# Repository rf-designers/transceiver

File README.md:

# YO6SSW SDR transceiver

Tayloe enabled SDR frontend.

## Designers

- Frédéric Boes
- Adrian Scripcă

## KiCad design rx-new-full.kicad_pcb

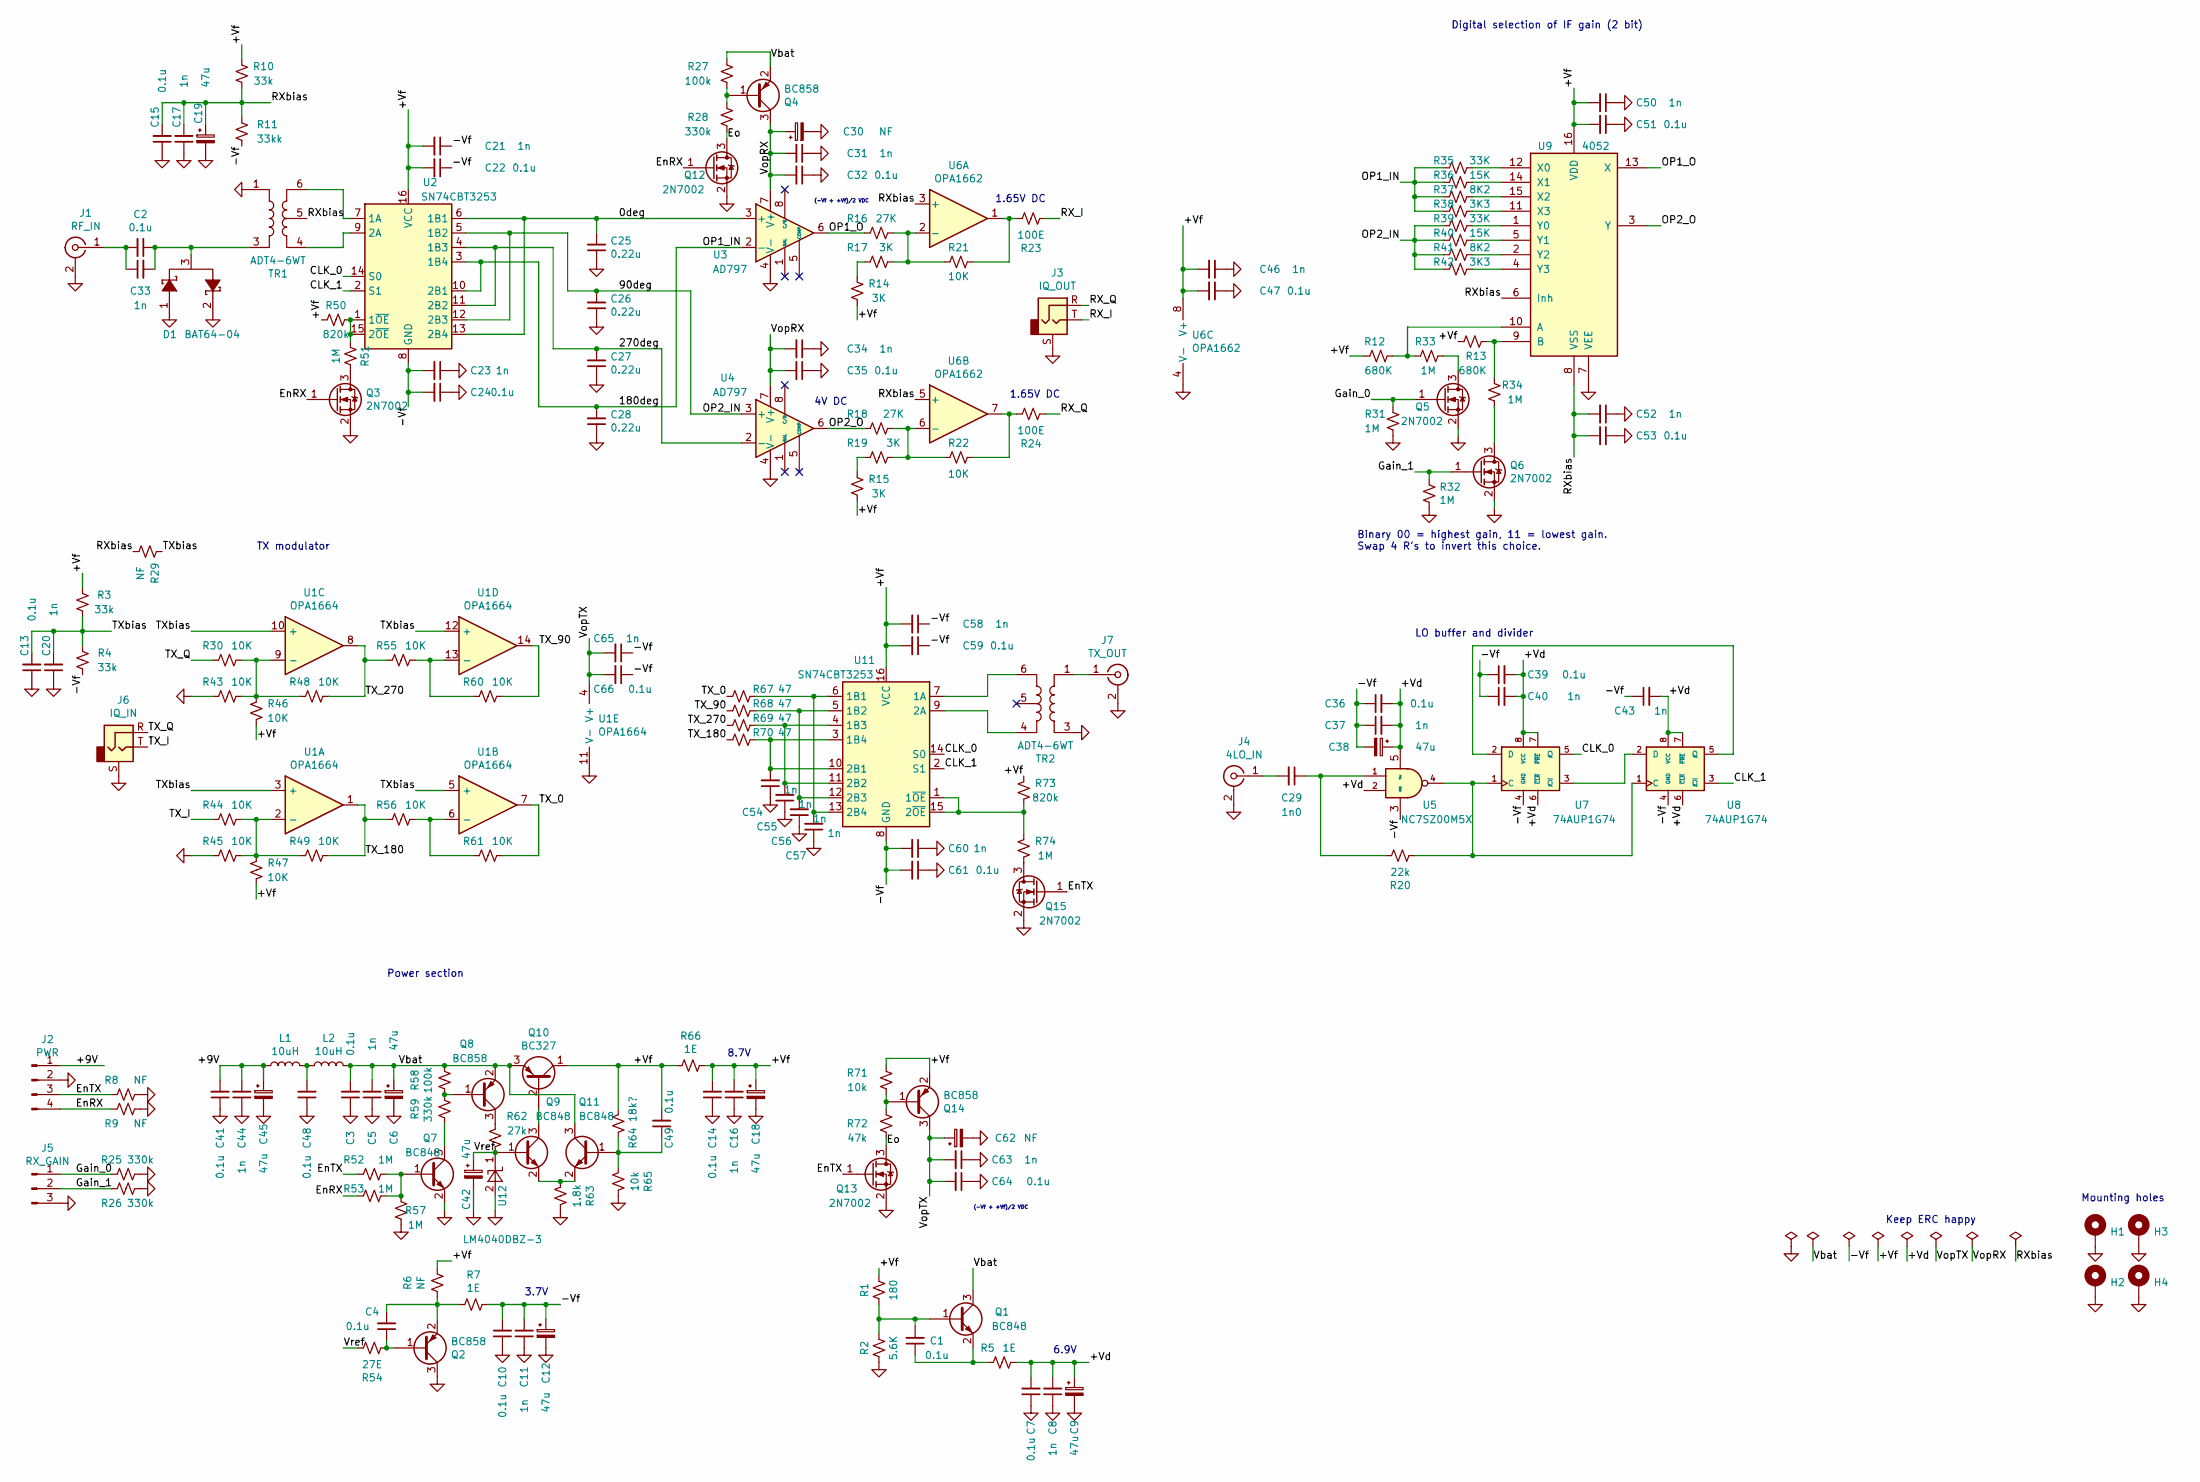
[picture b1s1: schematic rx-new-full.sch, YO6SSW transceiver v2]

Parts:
C1, C2, C3, C4, C7, C10, C13, C14, C15, C22, C24, C32, C35, C36, C39, C41, C47, C48, C49, C51, C53, C59, C61, C64, C66: 0.1u; C_0805_2012Metric_Pad1.15x1.40mm_HandSolder
C5, C8, C11, C16, C17, C20, C21, C23, C31, C33, C34, C37, C40, C43, C44, C46, C50, C52, C54, C55, C56, C57, C58, C60, C63, C65: 1n; C_0805_2012Metric_Pad1.15x1.40mm_HandSolder
C6, C9, C12, C18, C19, C38, C42, C45: 47u; CP_1210_3225Metric_Pad1.42x2.65mm_HandSolder
C25, C26, C27, C28: 0.22u; C_0805_2012Metric_Pad1.15x1.40mm_HandSolder
C29: 1n0; C_0805_2012Metric_Pad1.15x1.40mm_HandSolder
C30, C62: NF; CP_1210_3225Metric_Pad1.42x2.65mm_HandSolder
D1: BAT64-04; SOT-23
H1, H2, H3, H4: MountingHole_Pad; MountingHole_3.2mm_M3_DIN965_Pad
J1: RF_IN; SMA_Amphenol_901-144_Vertical
J2: PWR; PinHeader_1x04_P2.54mm_Vertical
J3: IQ_OUT; Jack_3.5mm_CUI_SJ1-3533NG_Horizontal; MPN SJ1-3533NG
J4: 4LO_IN; SMA_Amphenol_901-144_Vertical
J5: RX_GAIN; PinHeader_1x03_P2.54mm_Vertical
J6: IQ_IN; Jack_3.5mm_CUI_SJ1-3533NG_Horizontal; MPN SJ1-3533NG
J7: TX_OUT; SMA_Amphenol_901-144_Vertical
L1, L2: 10uH; L_0805_2012Metric_Pad1.15x1.40mm_HandSolder
Q1, Q7, Q9, Q11: BC848; SOT-23
Q2, Q4, Q8, Q14: BC858; SOT-23
Q3, Q5, Q6, Q12, Q13, Q15: 2N7002; SOT-23
Q10: BC327; TO-92_Inline
R1: 180; R_0805_2012Metric_Pad1.15x1.40mm_HandSolder
R2: 5.6K; R_0805_2012Metric_Pad1.15x1.40mm_HandSolder
R3, R4, R10: 33k; R_0805_2012Metric_Pad1.15x1.40mm_HandSolder
R5, R7, R66: 1E; R_0805_2012Metric_Pad1.15x1.40mm_HandSolder
R6, R8, R9, R29: NF; R_0805_2012Metric_Pad1.15x1.40mm_HandSolder
R11: 33kk; R_0805_2012Metric_Pad1.15x1.40mm_HandSolder
R12, R13: 680K; R_0805_2012Metric_Pad1.15x1.40mm_HandSolder
R14, R15, R17, R19: 3K; R_0805_2012Metric_Pad1.15x1.40mm_HandSolder
R16, R18: 27K; R_0805_2012Metric_Pad1.15x1.40mm_HandSolder
R20: 22k; R_0805_2012Metric_Pad1.15x1.40mm_HandSolder
R21, R22, R30, R43, R44, R45, R46, R47, R48, R49, R55, R56, R60, R61: 10K; R_0805_2012Metric_Pad1.15x1.40mm_HandSolder
R23, R24: 100E; R_0805_2012Metric_Pad1.15x1.40mm_HandSolder
R25, R26, R28, R59: 330k; R_0805_2012Metric_Pad1.15x1.40mm_HandSolder
R27, R58: 100k; R_0805_2012Metric_Pad1.15x1.40mm_HandSolder
R31, R32, R33, R34, R51, R52, R53, R57, R74: 1M; R_0805_2012Metric_Pad1.15x1.40mm_HandSolder
R35, R39: 33K; R_0805_2012Metric_Pad1.15x1.40mm_HandSolder
R36, R40: 15K; R_0805_2012Metric_Pad1.15x1.40mm_HandSolder
R37, R41: 8K2; R_0805_2012Metric_Pad1.15x1.40mm_HandSolder
R38, R42: 3K3; R_0805_2012Metric_Pad1.15x1.40mm_HandSolder
R50, R73: 820k; R_0805_2012Metric_Pad1.15x1.40mm_HandSolder
R54: 27E; R_0805_2012Metric_Pad1.15x1.40mm_HandSolder
R62: 27k; R_0805_2012Metric_Pad1.15x1.40mm_HandSolder
R63: 1.8k; R_0805_2012Metric_Pad1.15x1.40mm_HandSolder
R64: 18k?; R_0805_2012Metric_Pad1.15x1.40mm_HandSolder
R65, R71: 10k; R_0805_2012Metric_Pad1.15x1.40mm_HandSolder
R67, R68, R69, R70: 47; R_0805_2012Metric_Pad1.15x1.40mm_HandSolder
R72: 47k; R_0805_2012Metric_Pad1.15x1.40mm_HandSolder
TR1, TR2: ADT4-6WT; Mini-Circuits_CD636_H4.11mm
U1: OPA1664; SO-14_3.9x8.65mm_P1.27mm
U2, U11: SN74CBT3253; SOP-16_4.4x10.4mm_P1.27mm
U3, U4: AD797; SOIC-8_3.9x4.9mm_P1.27mm
U5: NC7SZ00M5X; SOT-23-5_HandSoldering
U6: OPA1662; SOIC-8_3.9x4.9mm_P1.27mm
U7, U8: 74AUP1G74; VSSOP-8_2.4x2.1mm_P0.5mm
U9: 4052; SOP-16_4.4x10.4mm_P1.27mm
U12: LM4040DBZ-3; SOT-23

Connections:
/0deg: C25.2, U2.6 (1B1), U2.13 (2B4), U3.3 (+)
/90deg: C26.2, R39.2, R40.2, R41.2, R42.2, U2.5 (1B2), U2.12 (2B3), U4.3 (+)
/180deg: C28.2, R35.2, R36.2, R37.2, R38.2, U2.3 (1B4), U2.10 (2B1), U3.2 (-); also elsewhere on the board
/270deg: C27.2, U2.4 (1B3), U2.11 (2B2), U4.2 (-); also elsewhere on the board
/+9V: C41.2, C44.2, C45.1, J2.1, L1.1
/+Vd: C7.2, C8.2, C9.1, C36.2, C37.2, C38.1, C39.2, C40.2, C43.2, R5.2, U5.2, U5.5 (Vcc), U7.6 (~CLR), U7.7 (~PRE), U7.8 (VCC), U8.6 (~CLR), U8.7 (~PRE), U8.8 (VCC)
/+Vf: C14.2, C16.2, C18.1, C21.2, C22.2, C46.2, C47.2, C49.2, C50.2, C51.2, C58.2, C59.2, Q10.1 (C), Q14.2 (E), R1.1, R3.2, R6.1, R10.2, R12.2, R13.2, R14.1, R15.1, R46.2, R47.2, R50.1, R64.1, R66.1, R66.2, R71.2, R73.1, U2.16 (VCC), U6.8 (V+), U9.16 (VDD), U11.16 (VCC); also elsewhere on the board
/-Vf: C10.2, C11.2, C12.1, C21.1, C22.1, C23.2, C24.2, C36.1, C37.1, C38.2, C39.1, C40.1, C43.1, C58.1, C59.1, C60.2, C61.2, C65.1, C66.1, R4.2, R7.1, R11.2, U2.8 (GND), U5.3 (GND), U7.4 (GND), U8.4 (GND), U11.8 (GND); also elsewhere on the board
/CLK_0: U2.14 (S0), U7.5 (Q), U11.14 (S0)
/CLK_1: U2.2 (S1), U8.3 (~Q), U11.2 (S1)
/EnRX: J2.4, Q3.1 (G), Q12.1 (G), R9.2, R53.1
/EnTX: J2.3, Q13.1 (G), Q15.1 (G), R8.2, R52.1
/Eo: Q12.3 (D), Q13.3 (D), R28.1, R72.1; also elsewhere on the board
/Gain_0: J5.1, Q5.1 (G), R25.2, R31.1
/Gain_1: J5.2, Q6.1 (G), R26.2, R32.1
/OP1_O: R16.1, U3.6, U9.13 (X)
/OP2_O: R18.1, U4.6, U9.3 (Y)
/RX_I: J3.T, R23.2
/RX_Q: J3.R, R24.2
/RXbias: C15.2, C17.2, C19.1, C52.2, C53.2, R10.1, R11.1, R29.1, TR1.5, U6.3 (+), U6.5 (+), U9.6 (Inh), U9.8 (VSS)
/TX_0: R61.1, R67.2, U1.7
/TX_90: R60.1, R68.2, U1.14
/TX_180: R49.1, R56.2, R70.2, U1.1
/TX_270: R48.1, R55.2, R69.2, U1.8
/TX_I: J6.T, R44.2
/TX_Q: J6.R, R30.2
/TXbias: C13.2, C20.2, R3.1, R4.1, R29.2, U1.3 (+), U1.5 (+), U1.10 (+), U1.12 (+)
/Vbat: C3.2, C5.2, C6.1, L2.2, Q1.3 (C), Q4.2 (E), Q8.2 (E), Q10.3 (E), Q11.3 (C), R27.2, R58.1; also elsewhere on the board
/VopRX: C30.1, C31.2, C32.2, C34.2, C35.2, Q4.3 (C), U3.7 (V+), U4.7 (V+)
/VopTX: C62.1, C63.2, C64.2, C65.2, C66.2, Q14.3 (C), U1.4 (V+)
/Vref: C42.1, Q9.1 (B), R54.1, R62.2, U12.1 (K)
GND: C3.1, C5.1, C6.2, C7.1, C8.1, C9.2, C10.1, C11.1, C12.2, C13.1, C14.1, C15.1, C16.1, C17.1, C18.2, C19.2, C20.1, C23.1, C24.1, C25.1, C26.1, C27.1, C28.1, C30.2, C31.1, C32.1, C34.1, C35.1, C41.1, C42.2, C44.1, C45.2, C46.1, C47.1, C48.1, C50.1, C51.1, C52.1, C53.1, C54.1, C55.1, C56.1, C57.1, C60.1, C61.1, C62.2, C63.1, C64.1, D1.1, D1.2, H1.1, H2.1, H3.1, H4.1, J1.2 (Ext), J2.2, J3.S, J4.2 (Ext), J5.3, J6.S, J7.2 (Ext), Q2.3 (C), Q3.2 (S), Q5.2 (S), Q6.2 (S), Q7.2 (E), Q12.2 (S), Q13.2 (S), Q15.2 (S), R2.2, R8.1, R9.1, R25.1, R26.1, R31.2, R32.2, R43.2, R45.2, R57.1, R63.2, R65.2, TR1.1, TR2.3, U1.11 (V-), U3.4 (V-), U4.4 (V-), U6.4 (V-), U9.7 (VEE), U12.2 (A); also elsewhere on the board
unnamed: C1.1, Q1.2 (E), R5.1
unnamed: C1.2, Q1.1 (B), R1.2, R2.1
unnamed: C2.1, C33.2, D1.3, TR1.3
unnamed: C2.2, C33.1, J1.1 (In)
unnamed 37: C4.1, Q2.1 (B), R54.2; also elsewhere on the board
unnamed: C4.2, Q2.2 (E), R6.2, R7.2
unnamed: C29.1, R20.1, U5.1
unnamed: C29.2, J4.1 (In)
unnamed: C48.2, L1.2, L2.1
unnamed: C49.1, Q11.1 (B), R64.2, R65.1
unnamed: C54.2, R70.1, U11.3 (1B4), U11.10 (2B1)
unnamed: C55.2, R69.1, U11.4 (1B3), U11.11 (2B2)
unnamed: C56.2, R68.1, U11.5 (1B2), U11.12 (2B3)
unnamed: C57.2, R67.1, U11.6 (1B1), U11.13 (2B4)
unnamed: J7.1 (In), TR2.1
unnamed: Q3.3 (D), R51.2
unnamed: Q4.1 (B), R27.1, R28.2
unnamed: Q5.3 (D), R33.1
unnamed: Q6.3 (D), R34.2
unnamed: Q7.1 (B), R52.2, R53.2, R57.2
unnamed: Q7.3 (C), R59.2
unnamed: Q8.1 (B), R58.2, R59.1
unnamed: Q8.3 (C), R62.1
unnamed: Q9.3 (C), Q10.2 (B)
unnamed: Q9.2 (E), Q11.2 (E), R63.1
unnamed: Q14.1 (B), R71.1, R72.2
unnamed: Q15.3 (D), R74.2
unnamed: R12.1, R33.2, U9.10 (A)
unnamed: R13.1, R34.1, U9.9 (B)
unnamed: R14.2, R17.1
unnamed: R15.2, R19.1
unnamed: R16.2, R17.2, R21.1, U6.2 (-)
unnamed: R18.2, R19.2, R22.1, U6.6 (-)
unnamed: R20.2, U5.4, U7.1 (C), U8.1 (C)
unnamed: R21.2, R23.1, U6.1
unnamed: R22.2, R24.1, U6.7
unnamed: R30.1, R43.1, R46.1, R48.2, U1.9 (-)
unnamed: R35.1, U9.12 (X0)
unnamed: R36.1, U9.14 (X1)
unnamed: R37.1, U9.15 (X2)
unnamed: R38.1, U9.11 (X3)
unnamed: R39.1, U9.1 (Y0)
unnamed: R40.1, U9.5 (Y1)
unnamed: R41.1, U9.2 (Y2)
unnamed: R42.1, U9.4 (Y3)
unnamed: R44.1, R45.1, R47.1, R49.2, U1.2 (-)
unnamed: R50.2, R51.1, U2.1 (1~OE), U2.15 (2~OE)
unnamed: R55.1, R60.2, U1.13 (-)
unnamed: R56.1, R61.2, U1.6 (-)
unnamed: R73.2, R74.1, U11.1 (1~OE), U11.15 (2~OE)
unnamed: TR1.4, U2.9 (2A)
unnamed: TR1.6, U2.7 (1A)
unnamed: TR2.4, U11.9 (2A)
unnamed: TR2.6, U11.7 (1A)
unnamed: U7.2 (D), U8.5 (Q)
unnamed: U7.3 (~Q), U8.2 (D)

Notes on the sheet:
Power section
3.7V
LO buffer and divider
(-Vf + +Vf)/2 VDC
1.65V DC
4V DC
Keep ERC happy
Mounting holes
8.7V
TX modulator
Binary 00 = highest gain, 11 = lowest gain. Swap 4 R's to invert this choice.
6.9V
Digital selection of IF gain (2 bit)

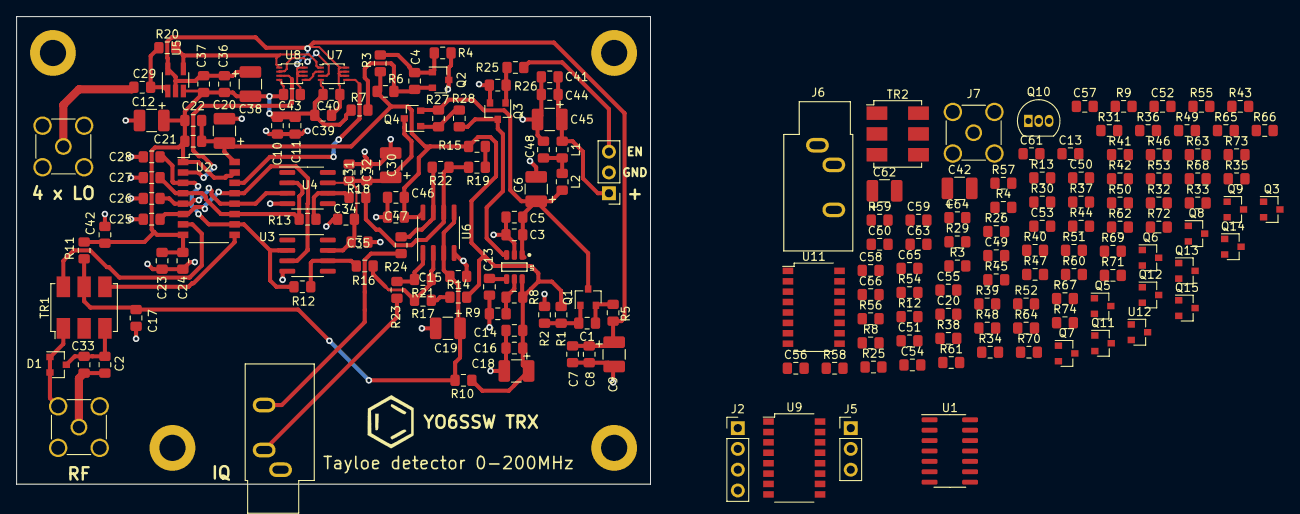
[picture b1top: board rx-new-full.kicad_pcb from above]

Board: 2 copper layers, 77.5 x 57.1 mm, 196 parts (0 on the bottom side), 92 nets.

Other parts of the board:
C13#2: 0.01u; C_0805_2012Metric_Pad1.15x1.40mm_HandSolder
C20#2: 47u; CP_1210_3225Metric_Pad1.42x2.65mm_HandSolder
C42#2: 1n; C_0805_2012Metric_Pad1.15x1.40mm_HandSolder
J2#2: PWR_IN; PinHeader_1x03_P2.54mm_Vertical
Q3#2: BC848; SOT-23
R3#2: 56k; R_0805_2012Metric_Pad1.15x1.40mm_HandSolder
R4#2: 6k8; R_0805_2012Metric_Pad1.15x1.40mm_HandSolder
R8#2: 120k; R_0805_2012Metric_Pad1.15x1.40mm_HandSolder
R9#2: 27k; R_0805_2012Metric_Pad1.15x1.40mm_HandSolder
R12#2, R13#2: 10k?; R_0805_2012Metric_Pad1.15x1.40mm_HandSolder
R25#2: 100k; R_0805_2012Metric_Pad1.15x1.40mm_HandSolder
R26#2: 10k; R_0805_2012Metric_Pad1.15x1.40mm_HandSolder
U1#2: TPS79101DBVREP; Texas_Instruments-TPS79101DBVREP-Level_A

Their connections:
/180deg: R12#2.1; also elsewhere on the board
/270deg: R13#2.1; also elsewhere on the board
/+Vf: C20#2.1, R3#2.1, R8#2.1, U1#2.6; also elsewhere on the board
/-Vf: C42#2.2; also elsewhere on the board
/En: J2#2.3, R25#2.1
/Eo: Q3#2.3, U1#2.3; also elsewhere on the board
/Vbat: U1#2.1; also elsewhere on the board
GND: C13#2.1, C20#2.2, C42#2.1, J2#2.2, Q3#2.2, R4#2.2, R9#2.2, R26#2.2, U1#2.2; also elsewhere on the board
unnamed 37: R3#2.2, R4#2.1; also elsewhere on the board
unnamed: C13#2.2, U1#2.4
unnamed: Q3#2.1, R25#2.2, R26#2.1
unnamed: R8#2.2, R9#2.1, U1#2.5

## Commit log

2020-09-07 WIP: laying out frontend schematic
2020-09-08 moved opamp
2020-09-08 Added some text
2020-09-11 created_basic_idea
2020-09-12 Added TPS79101 to custom library
2020-09-14 power_supplies
2020-09-14 opamps_buffer_errors
2020-09-14 Added custom symbols for flipflops and nand buffer
2020-09-14 level_shifter
2020-09-14 Converted labels to local labels, added supply capacitors and annotated components
2020-09-15 Added BAT64-04 at RF input
2020-09-15 Added connectors and made DRC happy
2020-09-15 enable_LCL_Less_elco
2020-09-16 Modified CLC to CLCLC, updated libraries, added En pin to power input connector
2020-09-21 Added 1210 CP footprint and created custom symbol for audio jack
2020-09-21 Added beginning of a layout
2020-09-30 WIP on layout
2020-09-30 some_layouting
2020-10-01 Layout: worked on power section
2020-10-01 Layout: more work
2020-10-02 finished_layout
2020-10-02 Fixed audio jack pin assignment
2020-10-02 Fixed DRC warning
2020-10-16 Added mounting holes and small layout changes
2020-10-20 changed_R_values
2020-11-13 Updated voltages and updated opamp feedbacks + reworked En section
2020-11-17 Reworked voltages and opamps resistors
2020-11-17 Added selectable RX gain
2020-11-18 WIP: added TX exciter draft
2020-11-19 changed_a_lot
2020-11-22 Annotations, cleaning up, made ERC pass
2021-06-01 Initial import
